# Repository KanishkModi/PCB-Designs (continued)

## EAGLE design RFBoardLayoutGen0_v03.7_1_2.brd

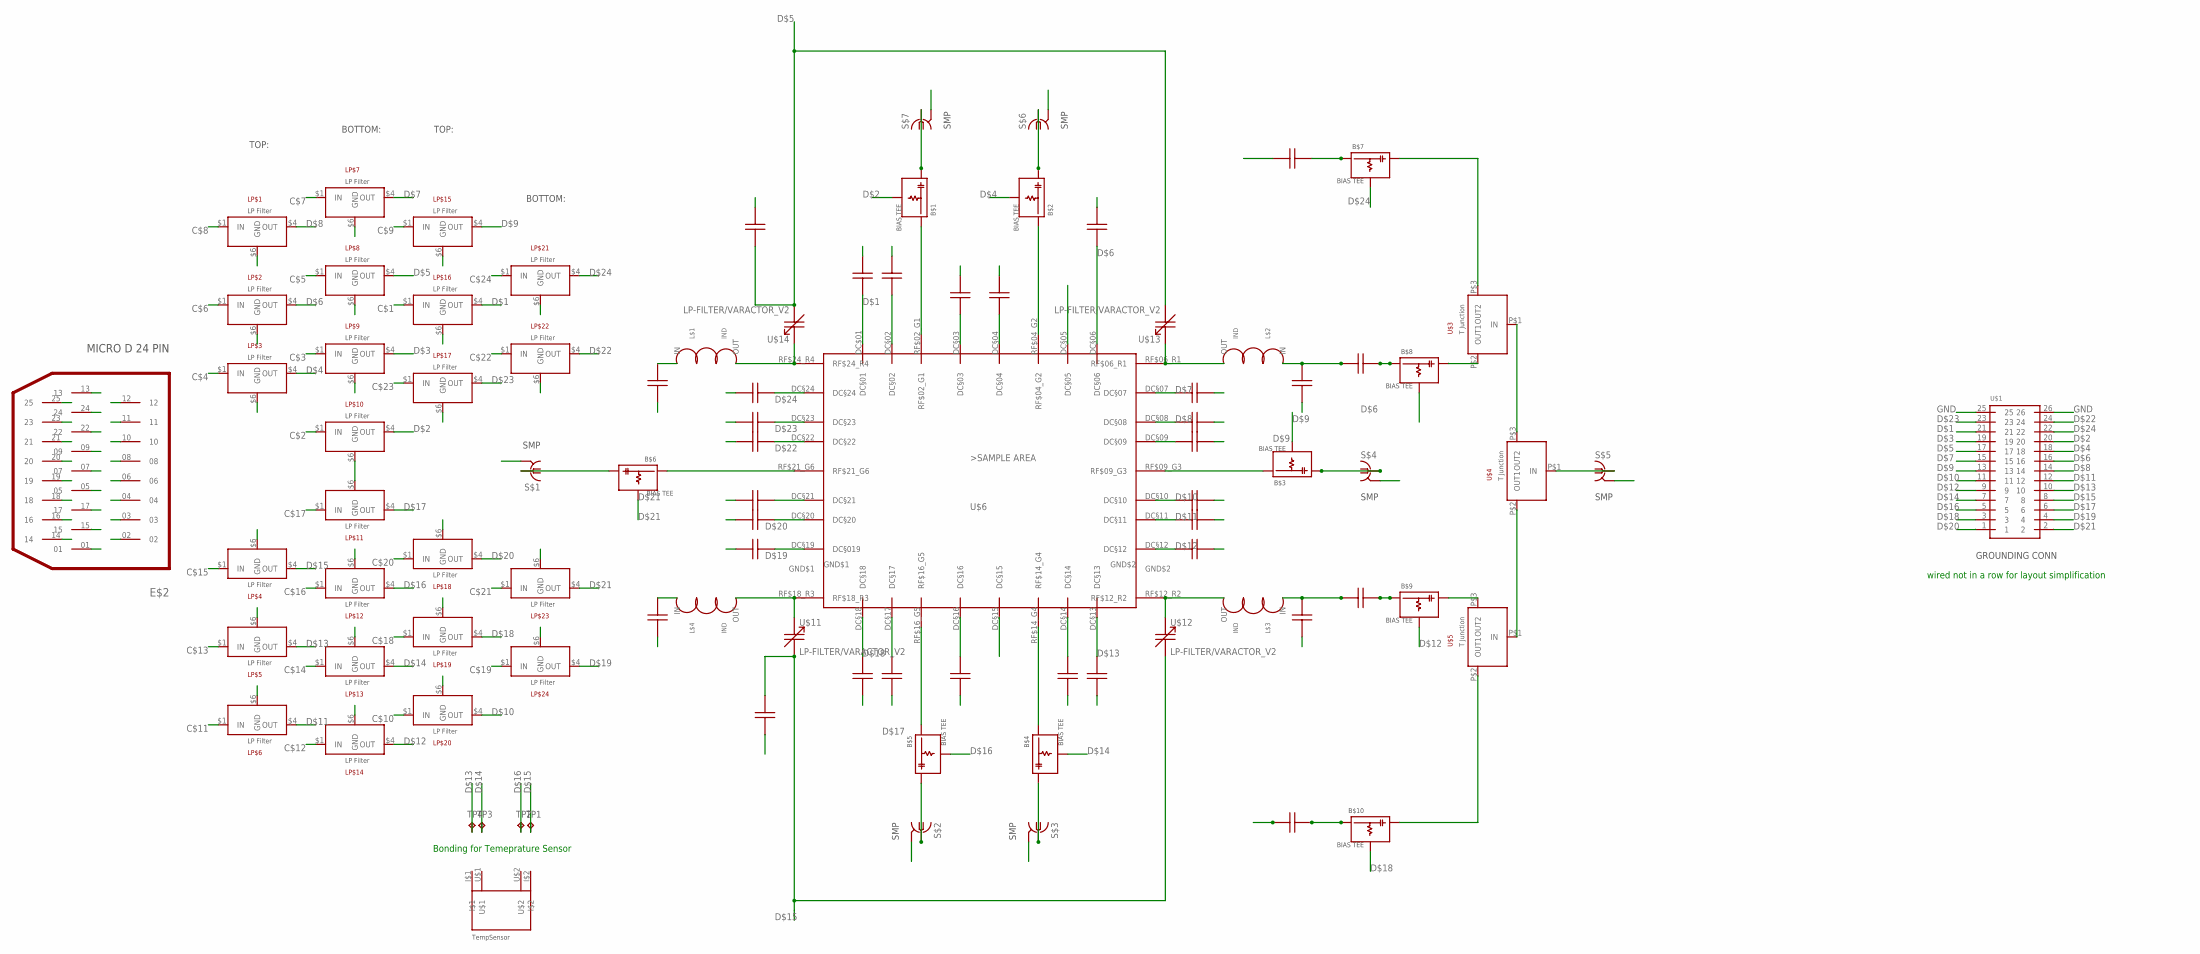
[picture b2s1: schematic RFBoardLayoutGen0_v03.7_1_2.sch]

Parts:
B$1: BIASTEEDOWN2; BIAS_TEE_DOWN_0603_V02
B$2, B$7, B$9: BIASTEEUP1; BIAS_TEE_UP_0603
B$3, B$4, B$6, B$8, B$10: BIASTEEDOWN1; BIAS_TEE_DOWN_0603
B$5: BIASTEEUP2; BIAS_TEE_UP_0603_V02
E$2: 25_SOCKET_M83513(13-DPINOUT2; 25_SOCKET_M83513/13-D_V2
L$1, L$2, L$3, L$4: L_MATCH
LP$1, LP$2, LP$3, LP$4, LP$5, LP$6, LP$15, LP$16, LP$17, LP$18, LP$19, LP$20: LP-FILTER/1-STAGETOP; LP-FILTER/1_STAGE/OS/0603_TOP
LP$7, LP$8, LP$9, LP$10, LP$11, LP$12, LP$13, LP$14, LP$21, LP$22, LP$23, LP$24: LP-FILTER/1-STAGEBOT; LP-FILTER/1_STAGE/OS/0603_BOTTOM
S$1, S$2, S$3, S$4, S$5, S$6, S$7: MC-921WIDE; SMP_STRAIGHT_MINI_WIDE
TP1, TP2, TP3, TP4: TPTP07SQ; TP07SQ
U$1: MEC8-113-02-L-D-RA1MBRD; MEC8-113-02-L-D-RA1
U$2: TEMPSENS; RX-BR_V1
U$3, U$4, U$5: TJUNCTION; T_JUNCTION_0.3MM
U$6: 24DC+10RF_V3.0; 24DC+10RF/400MU-PADS/0.7X0.7_V3.0
U$7, U$8, U$9, U$10, U$17, U$18, U$19, U$20: LP-FILTER/CAPACITOR/0603THIN; LP-FILTER/CAPACITOR/0603_BOTTOM
U$11, U$12, U$13, U$14: LP-FILTER/VARACTOR_V2
U$15, U$16, U$21, U$22, U$23, U$24, U$26, U$27, U$28, U$29, U$30, U$31, U$32, U$33, U$34, U$36, U$37, U$38, U$39, U$40, U$41, U$42, U$43, U$44: LP-FILTER/CAPACITOR/0603NORMAL; LP-FILTER/CAPACITOR/0603_BOTTOM_V2

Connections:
C$1: E$2.01, LP$16.$1 (IN)
C$2: E$2.02, LP$10.$1 (IN)
C$3: E$2.03, LP$9.$1 (IN)
C$4: E$2.04, LP$3.$1 (IN)
C$5: E$2.05, LP$8.$1 (IN)
C$6: E$2.06, LP$2.$1 (IN)
C$7: E$2.07, LP$7.$1 (IN)
C$8: E$2.08, LP$1.$1 (IN)
C$9: E$2.09, LP$15.$1 (IN)
C$10: E$2.10, LP$20.$1 (IN)
C$11: E$2.11, LP$6.$1 (IN)
C$12: E$2.12, LP$14.$1 (IN)
C$13: E$2.13, LP$5.$1 (IN)
C$14: E$2.14, LP$13.$1 (IN)
C$15: E$2.15, LP$4.$1 (IN)
C$16: E$2.16, LP$12.$1 (IN)
C$17: E$2.17, LP$11.$1 (IN)
C$18: E$2.18, LP$19.$1 (IN)
C$19: E$2.19, LP$24.$1 (IN)
C$20: E$2.20, LP$18.$1 (IN)
C$21: E$2.21, LP$23.$1 (IN)
C$22: E$2.22, LP$22.$1 (IN)
C$23: E$2.23, LP$17.$1 (IN)
C$24: E$2.24, LP$21.$1 (IN)
D$1: LP$16.$4 (OUT), U$1.21, U$6.DC$01 (DC§01), U$21.OUT (2)
D$2: B$1.LF, LP$10.$4 (OUT), U$1.20, U$6.DC§02, U$22.OUT (2)
D$3: LP$9.$4 (OUT), U$1.19, U$6.DC§03, U$23.OUT (2)
D$4: B$2.LF, LP$3.$4 (OUT), U$1.18, U$6.DC§04, U$24.OUT (2)
D$5: LP$8.$4 (OUT), U$1.17, U$6.DC§05, U$13.OUT1 (2), U$14.OUT1 (2), U$15.OUT (2)
D$6: B$8.LF, LP$2.$4 (OUT), U$1.16, U$6.DC§06, U$26.OUT (2)
D$7: LP$7.$4 (OUT), U$1.15, U$6.DC§07, U$27.OUT (2)
D$8: LP$1.$4 (OUT), U$1.14, U$6.DC§08, U$28.OUT (2)
D$9: B$3.LF, LP$15.$4 (OUT), U$1.13, U$6.DC§09, U$29.OUT (2)
D$10: LP$20.$4 (OUT), U$1.11, U$6.DC§10, U$30.OUT (2)
D$11: LP$6.$4 (OUT), U$1.12, U$6.DC§11, U$31.OUT (2)
D$12: B$9.LF, LP$14.$4 (OUT), U$1.9, U$6.DC§12, U$32.OUT (2)
D$13: LP$5.$4 (OUT), TP4.TP, U$1.10, U$6.DC§13, U$33.OUT (2)
D$14: B$4.LF, LP$13.$4 (OUT), TP3.TP, U$1.7, U$6.DC§14, U$34.OUT (2)
D$15: LP$4.$4 (OUT), TP1.TP, U$1.8, U$6.DC§15, U$11.OUT1 (2), U$12.OUT1 (2), U$16.OUT (2)
D$16: B$5.LF, LP$12.$4 (OUT), TP2.TP, U$1.5, U$6.DC§16, U$36.OUT (2)
D$17: LP$11.$4 (OUT), U$1.6, U$6.DC§17, U$37.OUT (2)
D$18: B$10.LF, LP$19.$4 (OUT), U$1.3, U$6.DC§18, U$38.OUT (2)
D$19: LP$24.$4 (OUT), U$1.4, U$6.DC§19 (DC§019), U$39.OUT (2)
D$20: LP$18.$4 (OUT), U$1.1, U$6.DC§20, U$40.OUT (2)
D$21: B$6.LF, LP$23.$4 (OUT), U$1.2, U$6.DC§21, U$41.OUT (2)
D$22: LP$22.$4 (OUT), U$1.24, U$6.DC§22, U$42.OUT (2)
D$23: LP$17.$4 (OUT), U$1.23, U$6.DC§23, U$43.OUT (2)
D$24: B$7.LF, LP$21.$4 (OUT), U$1.22, U$6.DC§24, U$44.OUT (2)
GND: E$2.25, LP$1.$6 (GND), LP$2.$6 (GND), LP$3.$6 (GND), LP$4.$6 (GND), LP$5.$6 (GND), LP$6.$6 (GND), LP$7.$6 (GND), LP$8.$6 (GND), LP$9.$6 (GND), LP$10.$6 (GND), LP$11.$6 (GND), LP$12.$6 (GND), LP$13.$6 (GND), LP$14.$6 (GND), LP$15.$6 (GND), LP$16.$6 (GND), LP$17.$6 (GND), LP$18.$6 (GND), LP$19.$6 (GND), LP$20.$6 (GND), LP$21.$6 (GND), LP$22.$6 (GND), LP$23.$6 (GND), LP$24.$6 (GND), S$1.2@1 (GND), S$1.2@2 (GND), S$2.2@1 (GND), S$2.2@2 (GND), S$3.2@1 (GND), S$3.2@2 (GND), S$4.2@1 (GND), S$4.2@2 (GND), S$5.2@1 (GND), S$5.2@2 (GND), S$6.2@1 (GND), S$6.2@2 (GND), S$7.2@1 (GND), S$7.2@2 (GND), U$1.25, U$1.26, U$7.OUT (2), U$8.OUT (2), U$9.OUT (2), U$10.OUT (2), U$15.IN (1), U$16.IN (1), U$21.IN (1), U$22.IN (1), U$23.IN (1), U$24.IN (1), U$26.IN (1), U$27.IN (1), U$28.IN (1), U$29.IN (1), U$30.IN (1), U$31.IN (1), U$32.IN (1), U$33.IN (1), U$34.IN (1), U$36.IN (1), U$37.IN (1), U$38.IN (1), U$39.IN (1), U$40.IN (1), U$41.IN (1), U$42.IN (1), U$43.IN (1), U$44.IN (1)
unnamed: B$6.HF, S$1.1
unnamed: L$3.OUT, U$6.RF$12_R2, U$12.OUT (1)
unnamed: B$6.OUT, U$6.RF$21_G6
unnamed: B$5.OUT, U$6.RF$16_G5
unnamed: B$1.HF, S$7.1
unnamed: B$2.HF, S$6.1
unnamed: B$4.OUT, U$6.RF$14_G4
unnamed: B$3.OUT, U$6.RF$09_G3
unnamed: L$4.OUT, U$6.RF$18_R3, U$11.OUT (1)
unnamed: L$1.OUT, U$6.RF$24_R4, U$14.OUT (1)
unnamed: L$2.OUT, U$6.RF$06_R1, U$13.OUT (1)
unnamed: B$2.OUT, U$6.RF$04_G2
unnamed: L$3.IN, U$9.IN (1), U$20.IN (1)
unnamed: L$2.IN, U$10.IN (1), U$19.IN (1)
unnamed: B$9.HF, U$5.P$3 (OUT2)
unnamed: B$5.HF, S$2.1
unnamed: B$4.HF, S$3.1
unnamed: B$3.HF, S$4.1
unnamed: B$7.HF, U$3.P$3 (OUT2)
unnamed: B$1.OUT, U$6.RF$02_G1
unnamed: S$5.1, U$4.P$1 (IN)
unnamed: B$10.HF, U$5.P$2 (OUT1)
unnamed: B$8.HF, U$3.P$2 (OUT1)
unnamed: B$8.OUT, U$19.OUT (2)
unnamed: U$3.P$1 (IN), U$4.P$3 (OUT2)
unnamed: U$4.P$2 (OUT1), U$5.P$1 (IN)
unnamed: B$9.OUT, U$20.OUT (2)
RF$3: L$4.IN, U$8.IN (1), U$18.IN (1)
RF$4: L$1.IN, U$7.IN (1), U$17.IN (1)
RF$31: B$10.OUT, U$18.OUT (2)
RF$41: B$7.OUT, U$17.OUT (2)

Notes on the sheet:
TOP:
BOTTOM:
Bonding for Temeprature Sensor
wired not in a row for layout simplification

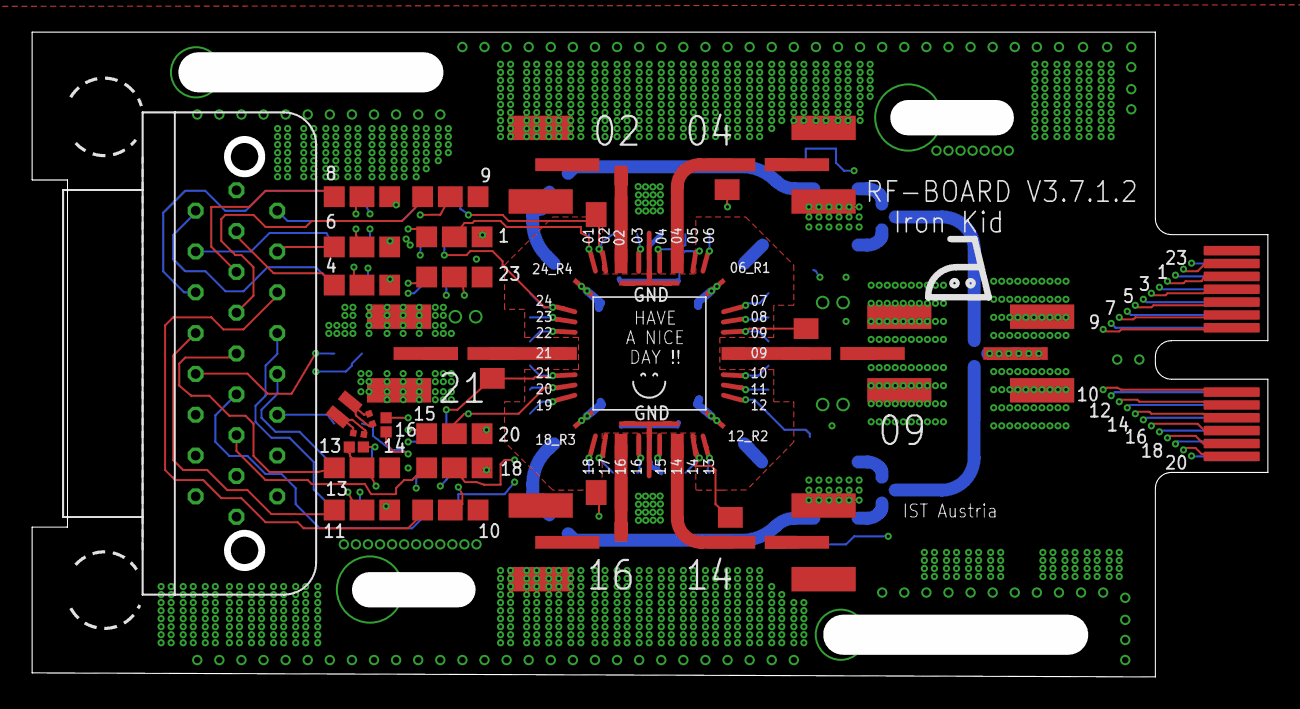
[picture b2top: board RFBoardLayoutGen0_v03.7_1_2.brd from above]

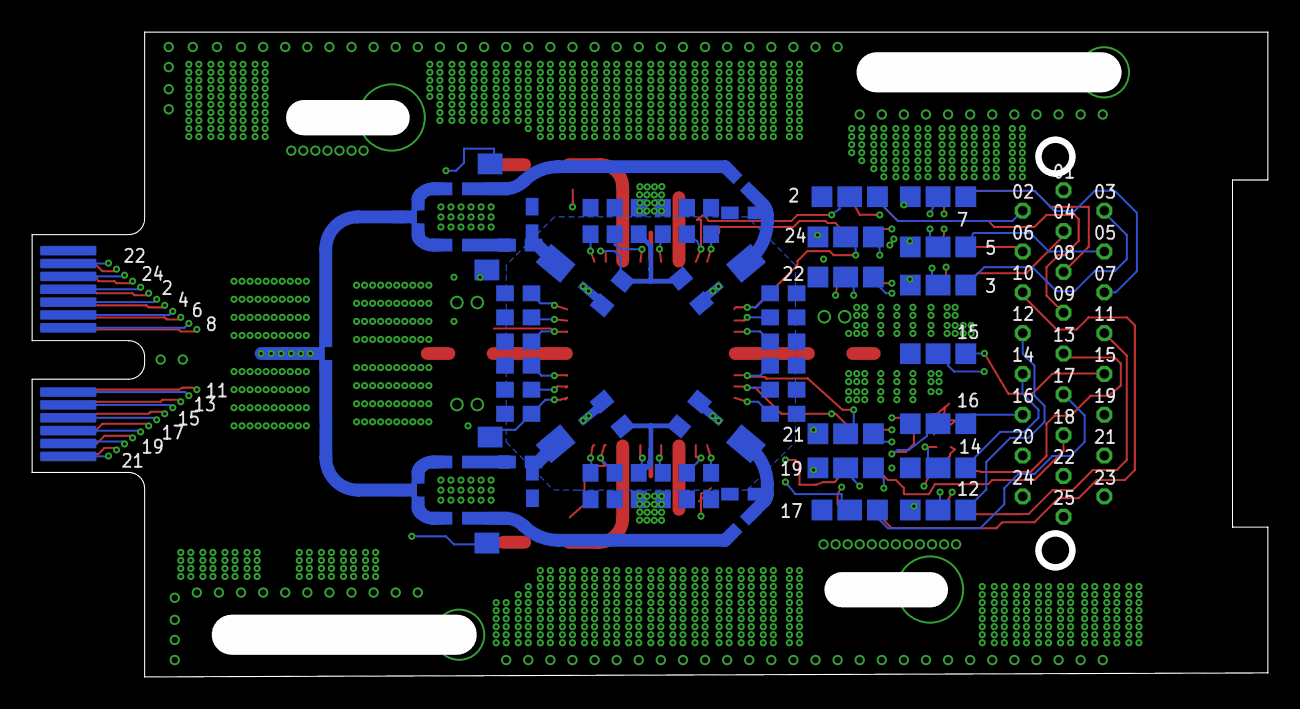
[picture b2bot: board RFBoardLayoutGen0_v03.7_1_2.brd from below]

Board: 6 copper layers, 76.9 x 40.1 mm, 92 parts (9 on the bottom side), 80 nets.

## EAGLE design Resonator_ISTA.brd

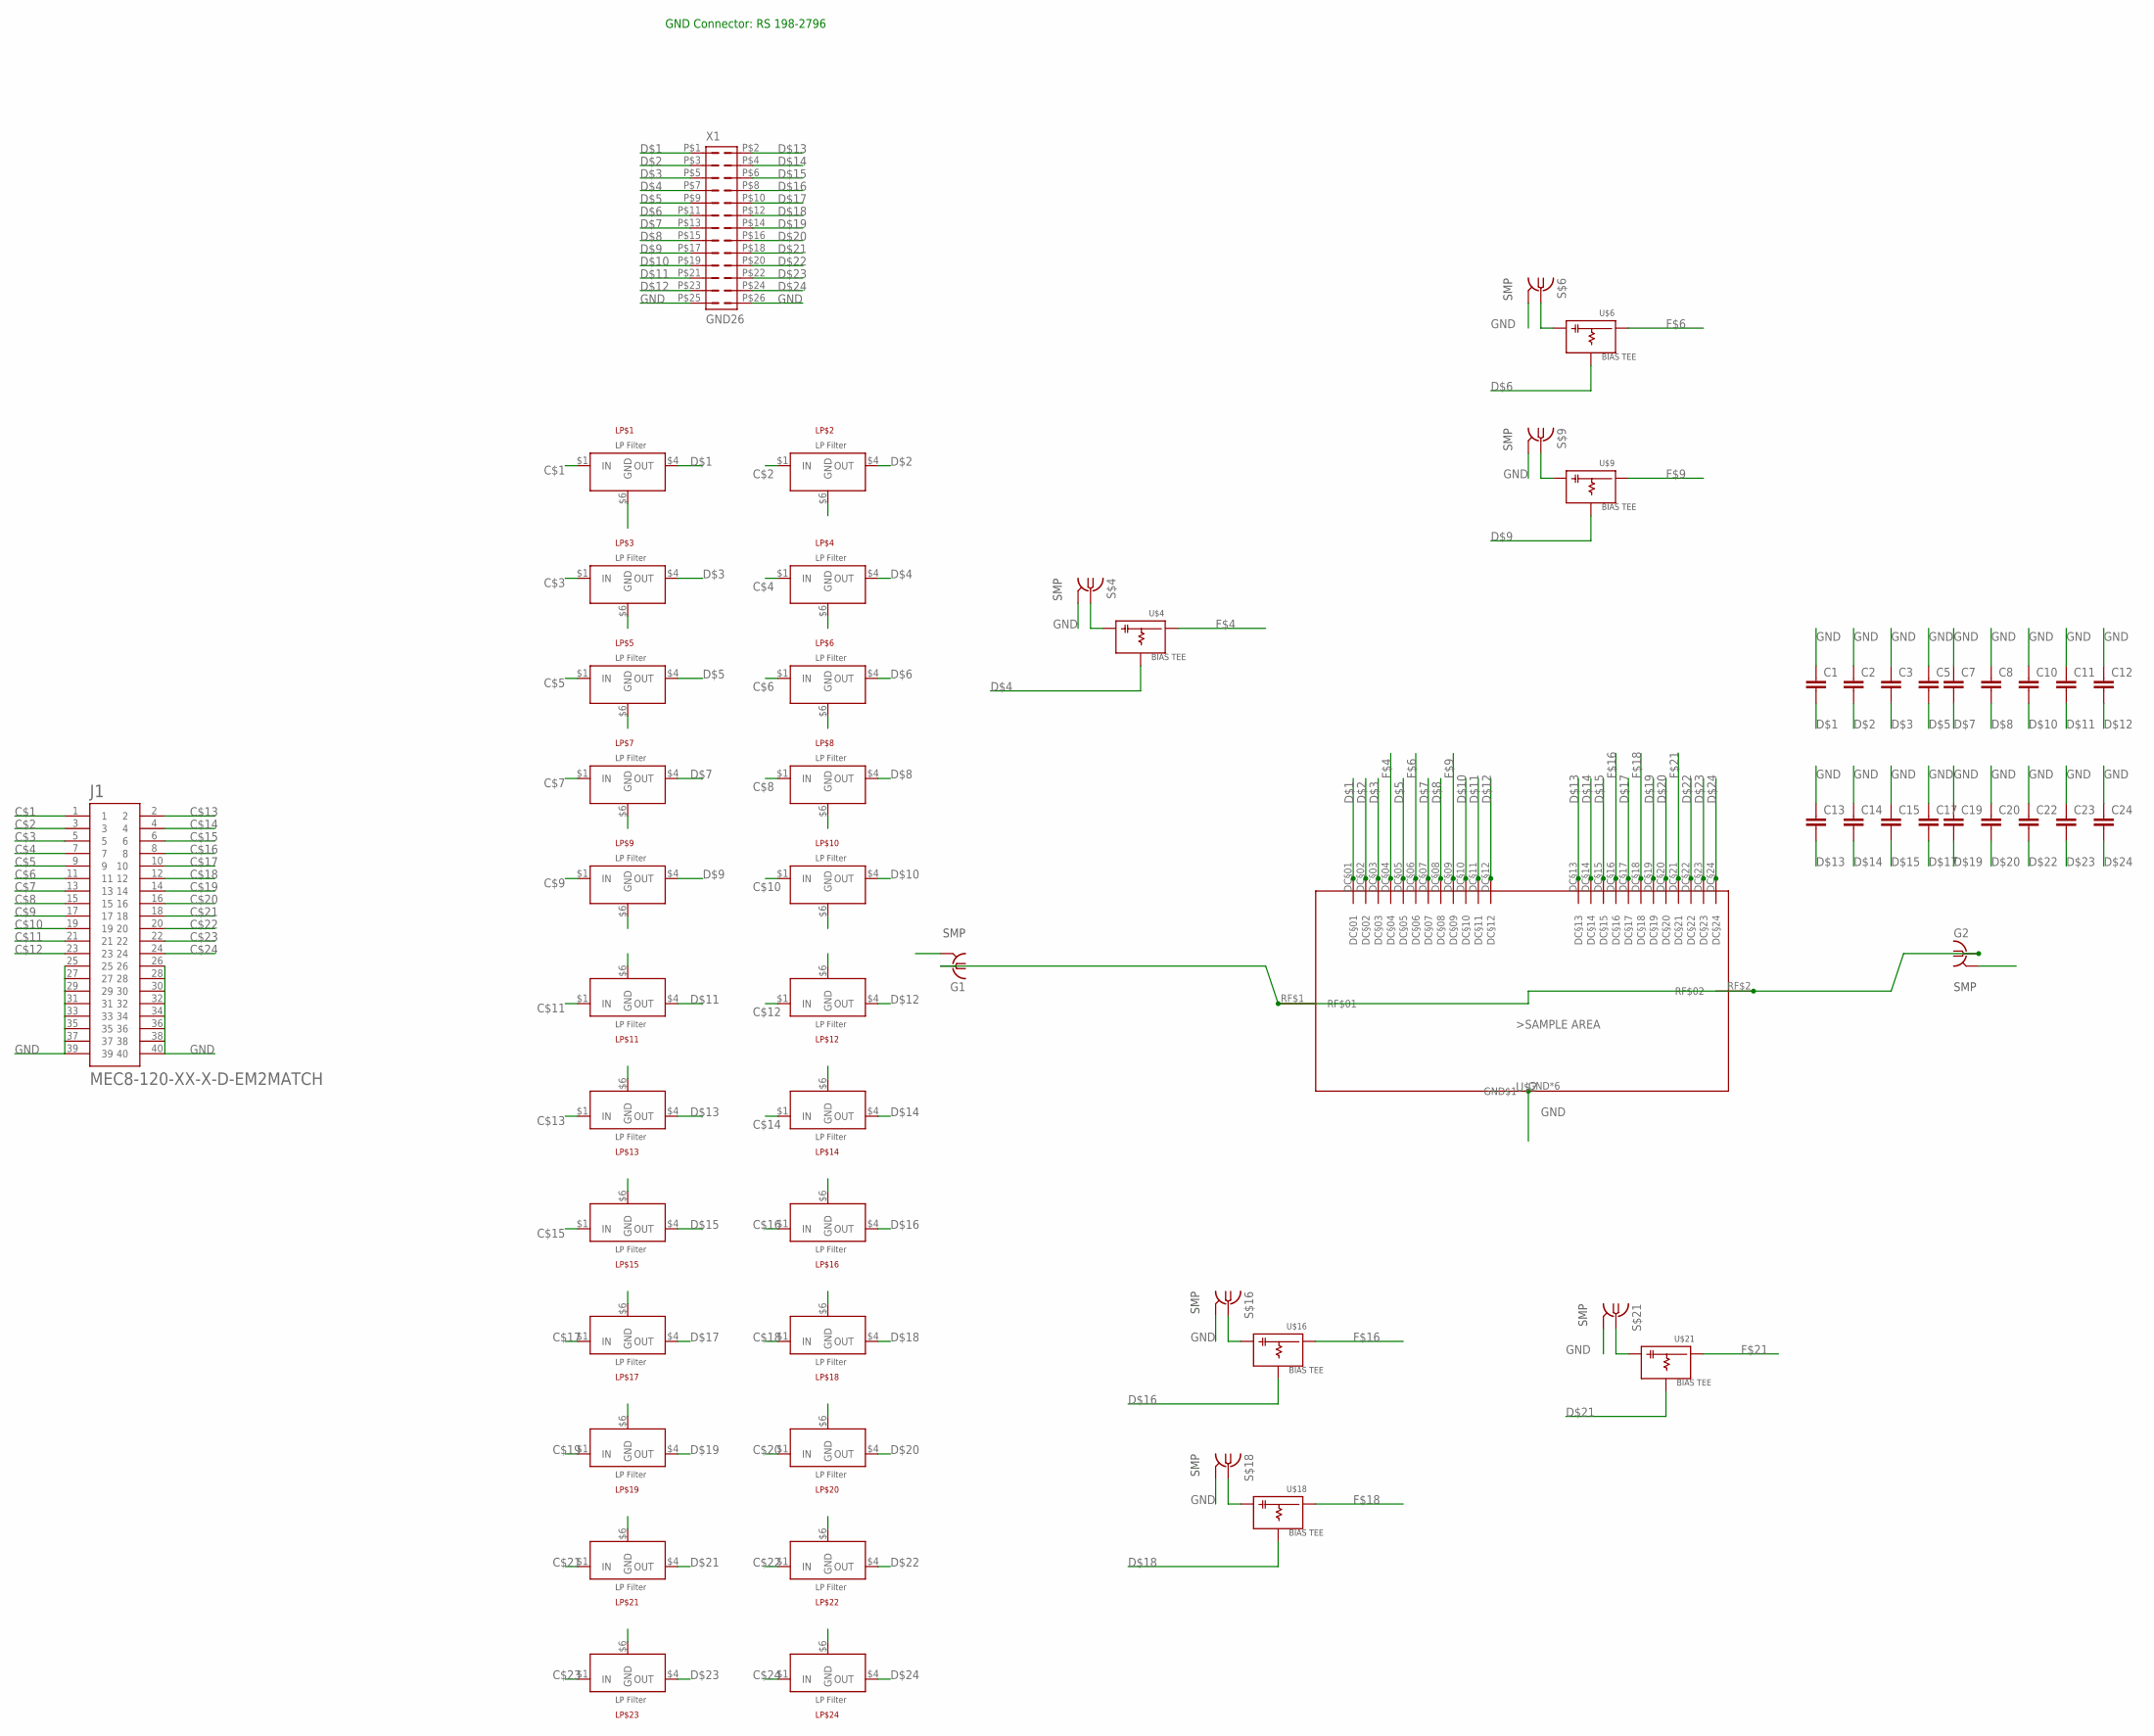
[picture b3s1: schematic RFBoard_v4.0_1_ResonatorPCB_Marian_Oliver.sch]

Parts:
C1, C2, C3, C5, C7, C8, C10, C11, C12, C13, C14, C15, C17, C19, C20, C22, C23, C24: C-EUC0805K; C0805K
G1, G2: MC-921; SMP_STRAIGHT_MINI_WIDE_V1_01_ROUND
J1: MEC8-120-XX-X-D-EM2MATCH; SAMTEC_MEC8-120-XX-X-D-EM2_MATCH
LP$1, LP$2, LP$9, LP$10, LP$11, LP$12, LP$13, LP$14, LP$15, LP$16, LP$17, LP$18, LP$19, LP$20, LP$21, LP$22, LP$23, LP$24: LP-FILTER/1-STAGETOP; LP-FILTER/1_STAGE/OS/0603_TOP
LP$3, LP$4, LP$5, LP$6, LP$7, LP$8: LP-FILTER/1-STAGEBOT; LP-FILTER/1_STAGE/OS/0603_BOTTOM
S$4, S$6, S$9, S$16, S$18, S$21: MC-921; SMP_STRAIGHT_MINI_WIDE_V1_01_ROUND
U$2: 24DC+4FAST+2RF_NO_HOLETEST; 24DC+4FASTGATE+2RF/6.0X6.0_V2.11
U$4, U$16, U$18: BIASTEETHINUP; BIAS_TEE_UP_0603_THIN
U$6, U$9, U$21: BIASTEETHIN; BIAS_TEE_DOWN_0603_THIN
X1: GND26; SMD2X13

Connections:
C$1: J1.1, LP$1.$1 (IN)
C$2: J1.3, LP$2.$1 (IN)
C$3: J1.5, LP$3.$1 (IN)
C$4: J1.7, LP$4.$1 (IN)
C$5: J1.9, LP$5.$1 (IN)
C$6: J1.11, LP$6.$1 (IN)
C$7: J1.13, LP$7.$1 (IN)
C$8: J1.15, LP$8.$1 (IN)
C$9: J1.17, LP$9.$1 (IN)
C$10: J1.19, LP$10.$1 (IN)
C$11: J1.21, LP$11.$1 (IN)
C$12: J1.23, LP$12.$1 (IN)
C$13: J1.2, LP$13.$1 (IN)
C$14: J1.4, LP$14.$1 (IN)
C$15: J1.6, LP$15.$1 (IN)
C$16: J1.8, LP$16.$1 (IN)
C$17: J1.10, LP$17.$1 (IN)
C$18: J1.12, LP$18.$1 (IN)
C$19: J1.14, LP$19.$1 (IN)
C$20: J1.16, LP$20.$1 (IN)
C$21: J1.18, LP$21.$1 (IN)
C$22: J1.20, LP$22.$1 (IN)
C$23: J1.22, LP$23.$1 (IN)
C$24: J1.24, LP$24.$1 (IN)
D$1: C1.2, LP$1.$4 (OUT), U$2.DC§01, X1.P$1 (1)
D$2: C2.2, LP$2.$4 (OUT), U$2.DC§02, X1.P$3 (3)
D$3: C3.2, LP$3.$4 (OUT), U$2.DC§03, X1.P$5 (5)
D$4: LP$4.$4 (OUT), U$4.LF, X1.P$7 (7)
D$5: C5.2, LP$5.$4 (OUT), U$2.DC§05, X1.P$9 (9)
D$6: LP$6.$4 (OUT), U$6.LF, X1.P$11 (11)
D$7: C7.2, LP$7.$4 (OUT), U$2.DC§07, X1.P$13 (13)
D$8: C8.2, LP$8.$4 (OUT), U$2.DC§08, X1.P$15 (15)
D$9: LP$9.$4 (OUT), U$9.LF, X1.P$17 (17)
D$10: C10.2, LP$10.$4 (OUT), U$2.DC§10, X1.P$19 (19)
D$11: C11.2, LP$11.$4 (OUT), U$2.DC§11, X1.P$21 (21)
D$12: C12.2, LP$12.$4 (OUT), U$2.DC§12, X1.P$23 (23)
D$13: C13.2, LP$13.$4 (OUT), U$2.DC§13, X1.P$2 (2)
D$14: C14.2, LP$14.$4 (OUT), U$2.DC§14, X1.P$4 (4)
D$15: C15.2, LP$15.$4 (OUT), U$2.DC§15, X1.P$6 (6)
D$16: LP$16.$4 (OUT), U$16.LF, X1.P$8 (8)
D$17: C17.2, LP$17.$4 (OUT), U$2.DC§17, X1.P$10 (10)
D$18: LP$18.$4 (OUT), U$18.LF, X1.P$12 (12)
D$19: C19.2, LP$19.$4 (OUT), U$2.DC§19, X1.P$14 (14)
D$20: C20.2, LP$20.$4 (OUT), U$2.DC§20, X1.P$16 (16)
D$21: LP$21.$4 (OUT), U$21.LF, X1.P$18 (18)
D$22: C22.2, LP$22.$4 (OUT), U$2.DC§22, X1.P$20 (20)
D$23: C23.2, LP$23.$4 (OUT), U$2.DC§23, X1.P$22 (22)
D$24: C24.2, LP$24.$4 (OUT), U$2.DC§24, X1.P$24 (24)
F$4: U$2.DC§04, U$4.OUT
F$6: U$2.DC§06, U$6.OUT
F$9: U$2.DC§09, U$9.OUT
F$16: U$2.DC§16, U$16.OUT
F$18: U$2.DC§18, U$18.OUT
F$21: U$2.DC§21, U$21.OUT
GND: C1.1, C2.1, C3.1, C5.1, C7.1, C8.1, C10.1, C11.1, C12.1, C13.1, C14.1, C15.1, C17.1, C19.1, C20.1, C22.1, C23.1, C24.1, G1.GND, G1.GND@1 (GND), G2.GND, G2.GND@1 (GND), J1.25, J1.26, J1.27, J1.28, J1.29, J1.30, J1.31, J1.32, J1.33, J1.34, J1.35, J1.36, J1.37, J1.38, J1.39, J1.40, LP$1.$6 (GND), LP$2.$6 (GND), LP$3.$6 (GND), LP$4.$6 (GND), LP$5.$6 (GND), LP$6.$6 (GND), LP$7.$6 (GND), LP$8.$6 (GND), LP$9.$6 (GND), LP$10.$6 (GND), LP$11.$6 (GND), LP$12.$6 (GND), LP$13.$6 (GND), LP$14.$6 (GND), LP$15.$6 (GND), LP$16.$6 (GND), LP$17.$6 (GND), LP$18.$6 (GND), LP$19.$6 (GND), LP$20.$6 (GND), LP$21.$6 (GND), LP$22.$6 (GND), LP$23.$6 (GND), LP$24.$6 (GND), S$4.GND, S$4.GND@1 (GND), S$6.GND, S$6.GND@1 (GND), S$9.GND, S$9.GND@1 (GND), S$16.GND, S$16.GND@1 (GND), S$18.GND, S$18.GND@1 (GND), S$21.GND, S$21.GND@1 (GND), U$2.GND (GND$1), U$2.GND1 (GND$1), U$2.GND2 (GND$1), U$2.GND3 (GND$1), U$2.GND4 (GND$1), U$2.GND5 (GND$1), X1.P$25 (25), X1.P$26 (26)
unnamed: S$16.1, U$16.HF
unnamed: S$21.1, U$21.HF
unnamed: S$4.1, U$4.HF
unnamed: S$9.1, U$9.HF
unnamed: G1.1, G2.1, U$2.RF$1 (RF$01), U$2.RF$2 (RF$02)
unnamed: S$6.1, U$6.HF
unnamed: S$18.1, U$18.HF

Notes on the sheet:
GND Connector: RS 198-2796

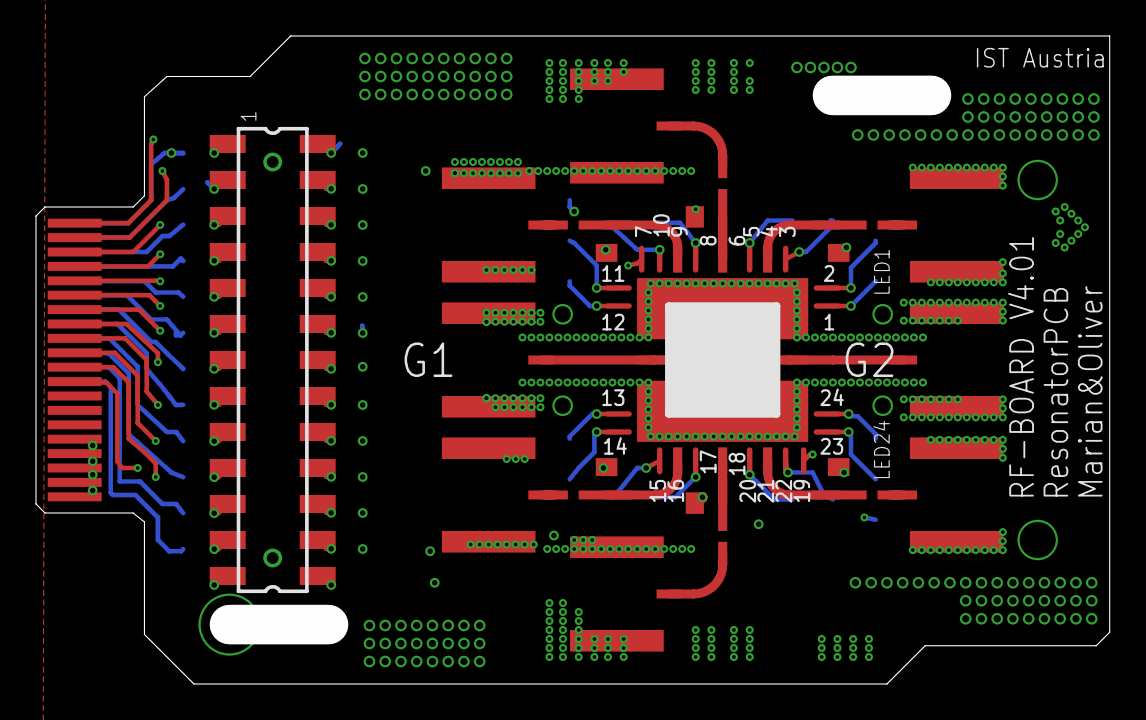
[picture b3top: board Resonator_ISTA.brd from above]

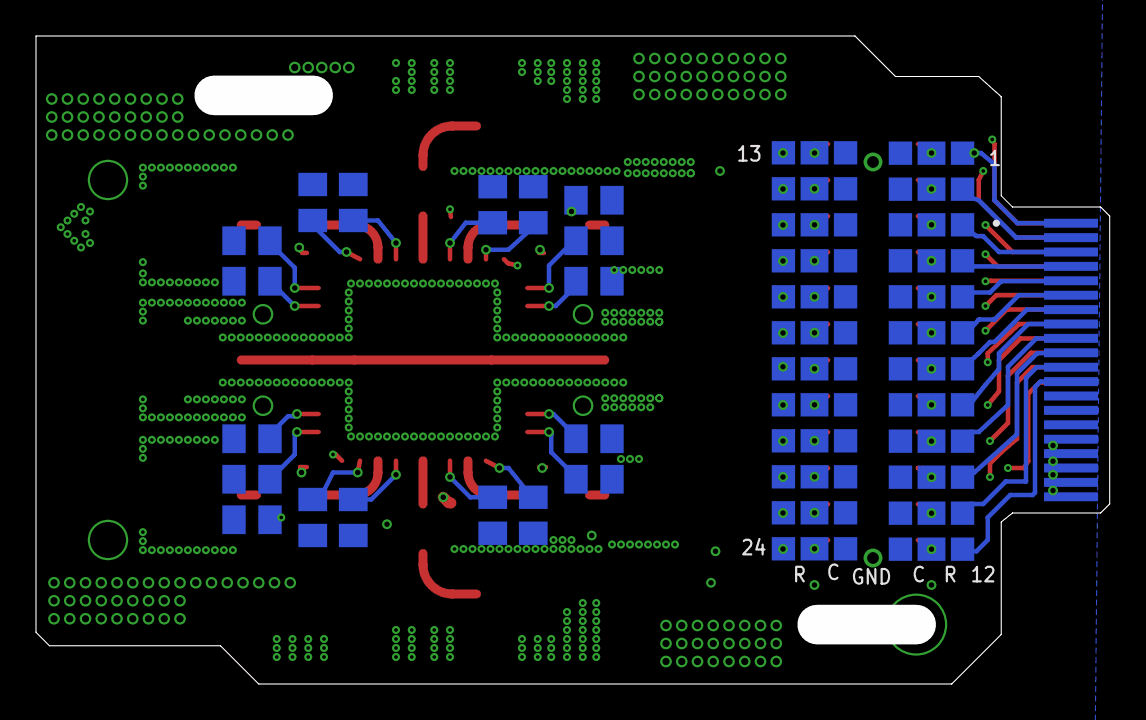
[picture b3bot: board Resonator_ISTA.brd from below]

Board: 6 copper layers, 59.6 x 36.0 mm, 59 parts (37 on the bottom side), 62 nets.

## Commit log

2025-07-01 Create Fat Papa (ISTA)
2025-07-01 Rename RFBoardLayoutGen0_v03.7_1_2.brd to IronKid_ISTA.brd
2025-07-01 Rename RFBoardLayoutGen0_v03.7_1_2.sch to IronKid_ISTA.sch
2025-07-01 Rename RFboardLeiden48_V_0.4.brd to FatPapa1_ISTA.brd
2025-07-01 Rename RFboardLeiden48_V_0.4.sch to FatPapa1_ISTA.sch
2025-07-01 Rename RFboardLeiden48_V_0.63.brd to FatPapa2_ISTA.brd
2025-07-01 Rename RFboardLeiden48_V_0.63.sch to FatPapa2_ISTA.sch
2025-07-01 Rename RFboardLeiden48_V_1.00.brd to FatPapa3_ISTA.brd
2025-07-01 Rename RFboardLeiden48_V_1.00.sch to FatPapa3_ISTA.sch
2025-07-01 Rename RFBoard_v4.0_1_ResonatorPCB_Marian_Oliver.brd to Resonator.brd
2025-07-01 Rename Resonator.brd to Resonator_ISTA.brd
2025-07-01 Rename RFBoard_v4.0_1_ResonatorPCB_Marian_Oliver.sch to Resonator_ISTA.sch
2025-07-01 Rename RFBoardLayoutGen0_v03.1.1_clean.brd to IronMan_ISTA.brd
2025-07-01 Rename RFBoardLayoutGen0_v03.1.1_clean.sch to IronMan_ISTA.sch
